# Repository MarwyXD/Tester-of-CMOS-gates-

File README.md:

# Tester-of-CMOS-gates-
# This is the tester of CMOS gates, they’re used a lot in electronics so i said to myself that i could create one, the reason i’m giving it online is that you all can later create code for your own CMOS gates, couse i only created program for six gates (7432, 7408, 4001, 7400, 7420, 7404/7414), i will later work on some more codes for this tester too, but for now i’ll keep it up to you, if you will create code for some more gates.

# As i mentioned in the discription of the eagle files, you should only use the .sch file, the board isn’t finished, it is due to i selected to only route the bottom layer (i dont have any PCBs with two layers), but you can create gerber files and send it for example to JLC PCB, they will do it very precisly (probably).

# The tester_CMOS_hradel.ino file is my original code for the tester. 

# Thank you.

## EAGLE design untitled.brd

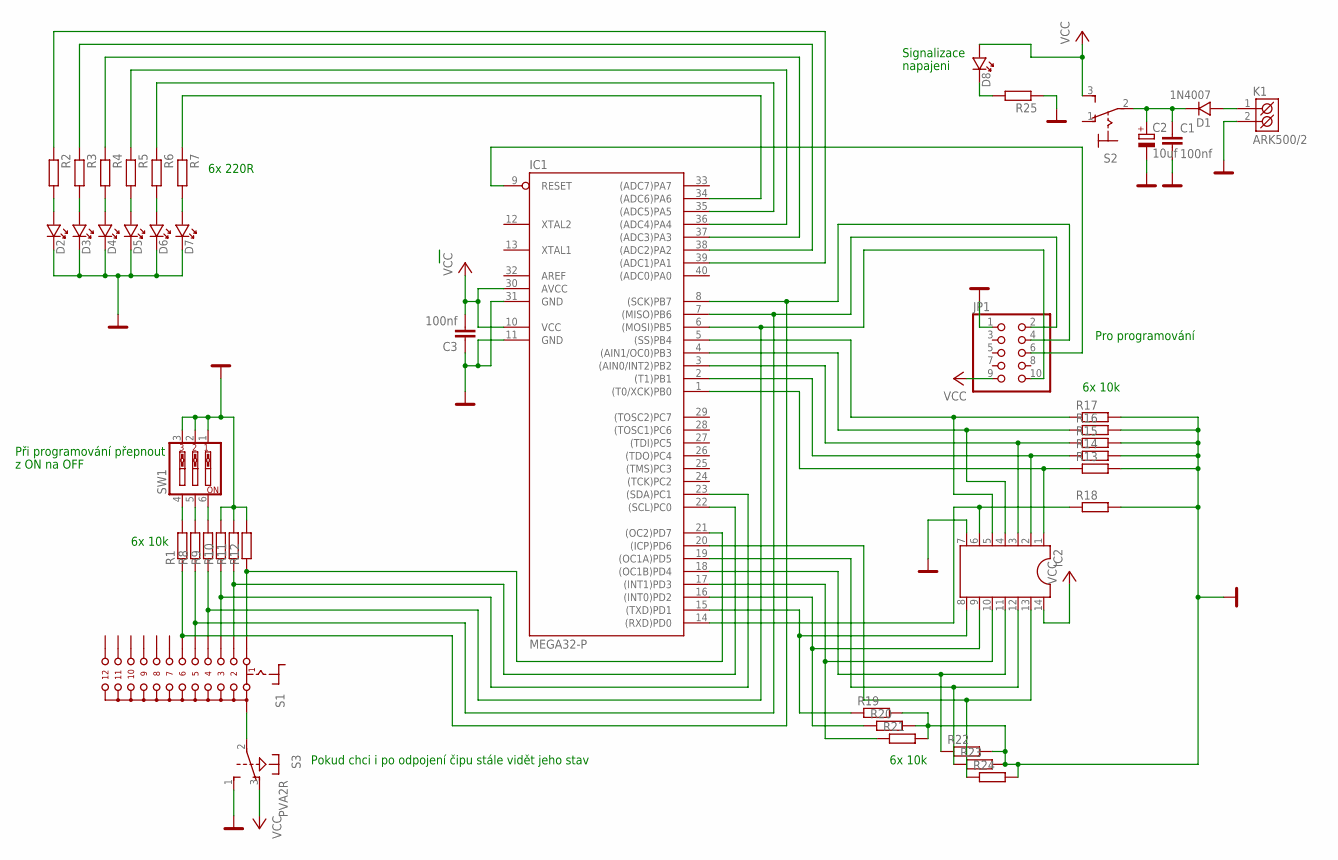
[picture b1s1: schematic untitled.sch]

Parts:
C1, C3: 100nf; C050-025X075
C2: 10uf; E5-8,5
D1: 1N4007; DO41
D2, D3, D4, D5, D6, D7, D8: LED_5
IC1: MEGA32-P; DIL40
IC2: DIL14
JP1: PINHD-2X5; 2X05
K1: ARK500/2
R1, R2, R3, R4, R5, R6, R7, R8, R9, R10, R11, R12, R13, R14, R15, R16, R17, R18, R19, R20, R21, R22, R23, R24, R25: R-EU_0207/10; 0207/10
S1: CK101X12
S2: 320-916
S3: PVA2R
SW1: SW_DIP-3; EDG-03

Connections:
GND: C1.2, C2.-, C3.1, D2.K, D3.K, D4.K, D5.K, D6.K, D7.K, IC1.11 (GND), IC1.31 (GND), IC2.7, JP1.1, K1.2 (K2), R10.2, R11.2, R12.2, R13.2, R14.2, R15.2, R16.2, R17.2, R18.2, R19.2, R20.2, R21.2, R22.2, R23.2, R24.2, R25.1, S3.1 (S), SW1.1, SW1.2, SW1.3
unnamed: R1.2, SW1.4
unnamed: D2.A, R2.2
unnamed: D3.A, R3.2
unnamed: D4.A, R4.2
unnamed: S1.A, S3.2
unnamed: IC1.1 ((T0/XCK)PB0), IC2.1, R13.1
unnamed: IC1.8 ((SCK)PB7), JP1.4, R1.1, S1.6
unnamed: IC1.9 (RESET), JP1.6
unnamed: D5.A, R5.2
unnamed: R8.2, SW1.5
unnamed: R9.2, SW1.6
unnamed: D6.A, R6.2
unnamed: D7.A, R7.2
unnamed: IC1.39 ((ADC1)PA1), R2.1
unnamed: IC1.38 ((ADC2)PA2), R3.1
unnamed: IC1.37 ((ADC3)PA3), R4.1
unnamed: IC1.36 ((ADC4)PA4), R5.1
unnamed: IC1.35 ((ADC5)PA5), R6.1
unnamed: IC1.34 ((ADC6)PA6), R7.1
unnamed: IC1.2 ((T1)PB1), IC2.2, R14.1
unnamed: IC1.7 ((MISO)PB6), JP1.2, R8.1, S1.5
unnamed: IC1.6 ((MOSI)PB5), JP1.10, R9.1, S1.4
unnamed: IC1.23 ((SDA)PC1), R10.1, S1.3
unnamed: IC1.22 ((SCL)PC0), R11.1, S1.2
unnamed: IC1.21 ((OC2)PD7), R12.1, S1.1
unnamed: IC1.3 ((AIN0/INT2)PB2), IC2.3, R15.1
unnamed: IC1.4 ((AIN1/OC0)PB3), IC2.4, R16.1
unnamed: IC1.5 ((SS)PB4), IC2.5, R17.1
unnamed: IC1.14 ((RXD)PD0), IC2.6, R18.1
unnamed: C1.1, C2.+, D1.K, S2.2
unnamed: D1.A, K1.1 (K1)
unnamed: IC1.15 ((TXD)PD1), IC2.8, R19.1
unnamed: IC1.16 ((INT0)PD2), IC2.9, R20.1
unnamed: IC1.17 ((INT1)PD3), IC2.10, R21.1
unnamed: IC1.18 ((OC1B)PD4), IC2.11, R22.1
unnamed: IC1.19 ((OC1A)PD5), IC2.12, R23.1
unnamed: IC1.20 ((ICP)PD6), IC2.13, R24.1
unnamed: D8.K, R25.2
VCC: C3.2, D8.A, IC1.10 (VCC), IC1.30 (AVCC), IC2.14, JP1.9, S2.3 (S), S3.3 (O)

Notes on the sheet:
6x 10k
6x 220R
Při programování přepnout
z ON na OFF
Pokud chci i po odpojení čipu stále vidět jeho stav
Signalizace
napajeni
Pro programování

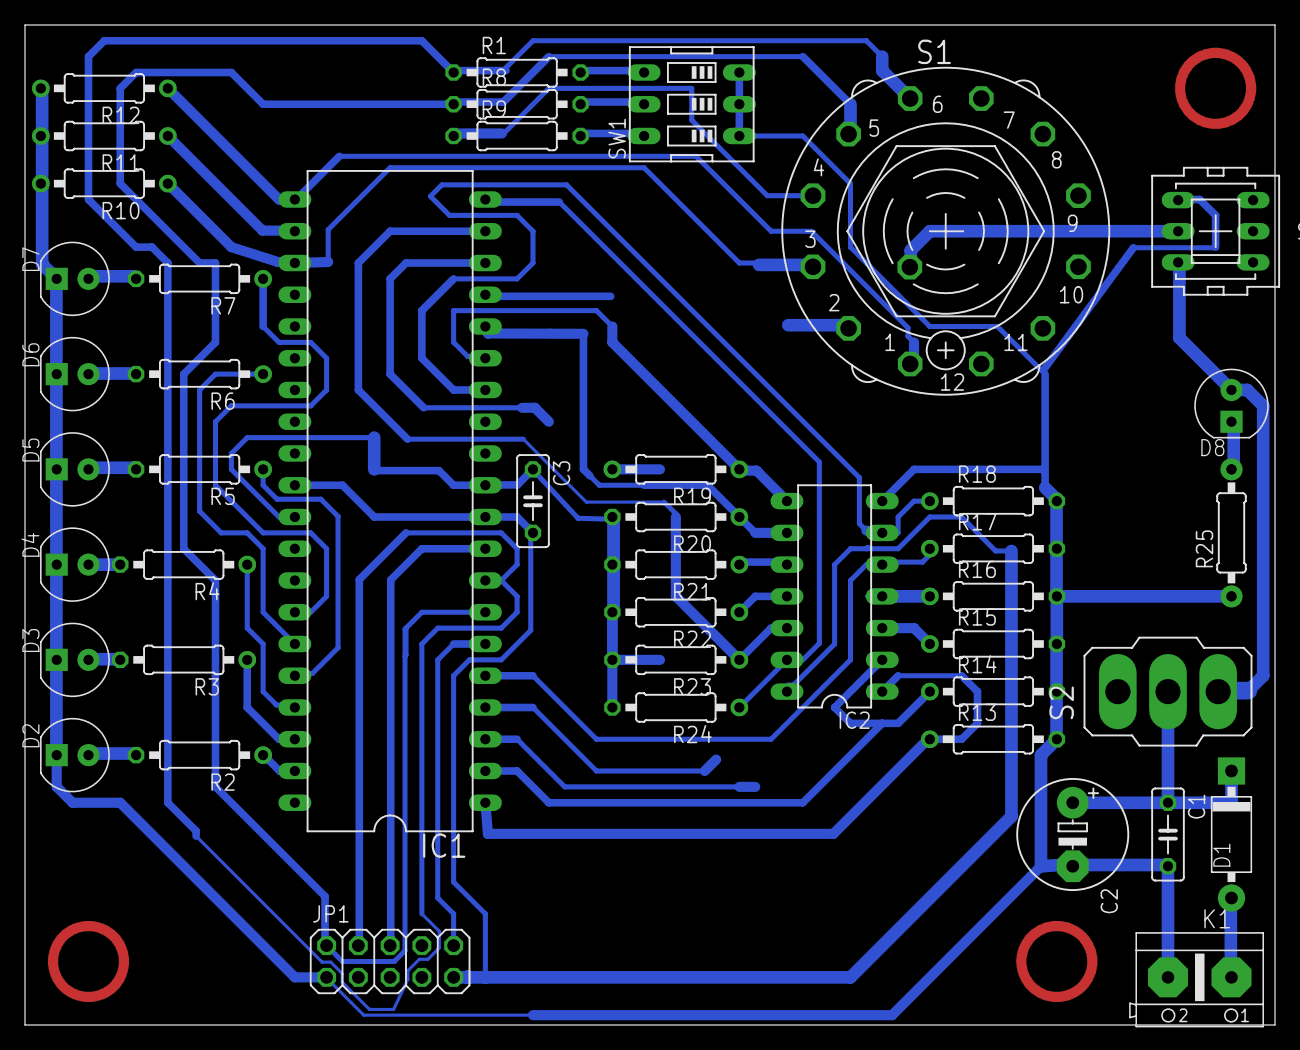
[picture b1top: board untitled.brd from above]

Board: 2 copper layers, 100.0 x 80.0 mm, 44 parts (0 on the bottom side), 40 nets.

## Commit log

2021-06-14 The documentation for the IO’s
2021-06-14 Schematics and board layout in eagle
    This is what i create for it, firstly i want to recomend to you to only use the .sch file, you can create your own PCB, there are some traces that even the autorouter wasn’t able to do (unrouted), so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

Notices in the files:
parts and their libraries:
Copyright (C) PaJa 2001-2014
Copyright (C) PaJa 2011-2014
